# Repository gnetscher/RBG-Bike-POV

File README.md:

RBG-Bike-POV
============

Created for the TI Intern Design Contest 2012

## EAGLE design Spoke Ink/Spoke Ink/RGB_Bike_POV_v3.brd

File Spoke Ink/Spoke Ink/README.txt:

This project was completed in a 5 week time frame.  Please, forgive the somewhat
convoluted nature of our software. finalmainwithstatemachine.c and finalnostatemachine.c both 
contain working versions of our code, but do slightly different things.  With state machine, 
cycles through 3 differnt colored images, and no state machine project one multicolered image.
Thank you for checking out Spoke Ink!

All the best,
George, Val, and Ryan

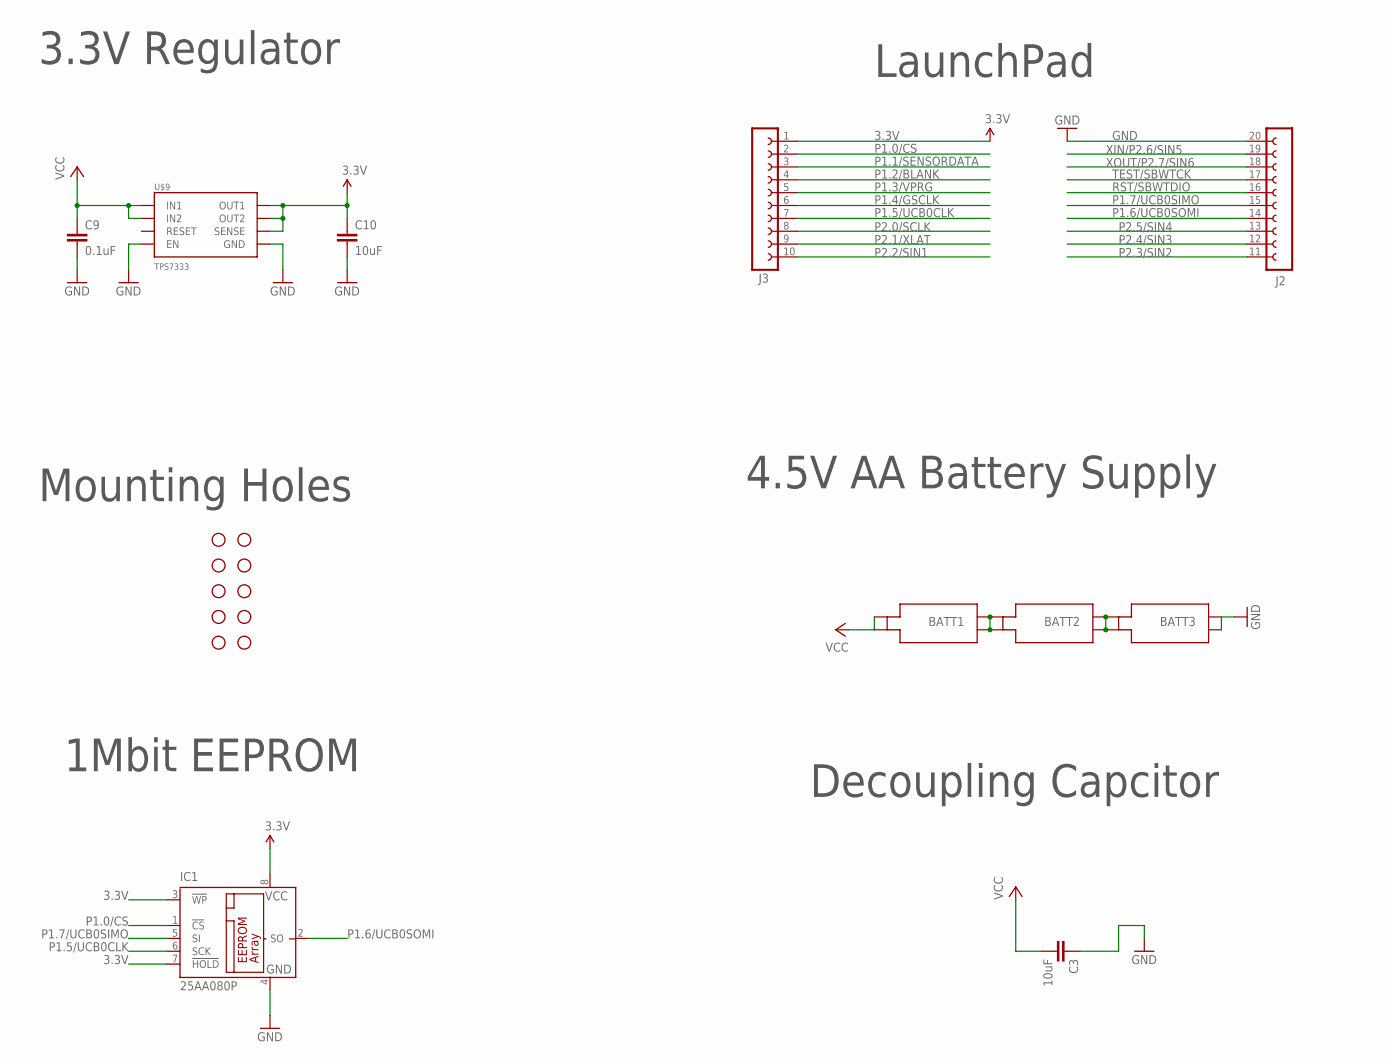
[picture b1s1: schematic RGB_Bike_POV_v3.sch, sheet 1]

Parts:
BATT1, BATT2, BATT3: 1XAA
C3, C10: 10uF; CAP-PTH-SMALL
C9: 0.1uF; CAP-PTH-SMALL
IC1: 25AA080P; DIL8
J2: FE10H
J3: FE10L; FE10
JP1, JP2, JP3, JP4, JP5, JP7, JP25, JP26, JP27, JP28: STAND-OFF
U$9: TPS7333

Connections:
3.3V: C10.1, IC1.3 (!WP), IC1.7 (!HOLD), IC1.8 (VCC), J3.1, U$9.5 (OUT1), U$9.6 (OUT2), U$9.7 (SENSE); also elsewhere on the board
GND: BATT3.N1, BATT3.N2, C3.1, C9.2, C10.2, IC1.4 (GND), J2.20 (10), U$9.1 (GND), U$9.2 (EN); also elsewhere on the board
unnamed: BATT1.N1, BATT1.N2, BATT2.P1, BATT2.P2
unnamed: BATT2.N1, BATT2.N2, BATT3.P1, BATT3.P2
P1.0/CS: IC1.1 (!CS), J3.2
P1.1/SENSORDATA: J3.3; also elsewhere on the board
P1.2/BLANK: J3.4; also elsewhere on the board
P1.3/VPRG: J3.5; also elsewhere on the board
P1.4/GSCLK: J3.6; also elsewhere on the board
P1.5/UCB0CLK: IC1.6 (SCK), J3.7
P1.6/UCB0SOMI: IC1.2 (SO), J2.14 (4)
P1.7/UCB0SIMO: IC1.5 (SI), J2.15 (5)
P2.0/SCLK: J3.8; also elsewhere on the board
P2.1/XLAT: J3.9; also elsewhere on the board
P2.2/SIN1: J3.10; also elsewhere on the board
P2.3/SIN2: J2.11 (1); also elsewhere on the board
P2.4/SIN3: J2.12 (2); also elsewhere on the board
P2.5/SIN4: J2.13 (3); also elsewhere on the board
RST/SBWTDIO: J2.16 (6)
TEST/SBWTCK: J2.17 (7)
VCC: BATT1.P1, BATT1.P2, C3.2, C9.1, U$9.3 (IN1), U$9.4 (IN2); also elsewhere on the board
XIN/P2.6/SIN5: J2.19 (9); also elsewhere on the board
XOUT/P2.7/SIN6: J2.18 (8); also elsewhere on the board

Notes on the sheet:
Mounting Holes
3.3V Regulator
LaunchPad
4.5V AA Battery Supply
1Mbit EEPROM
Decoupling Capcitor

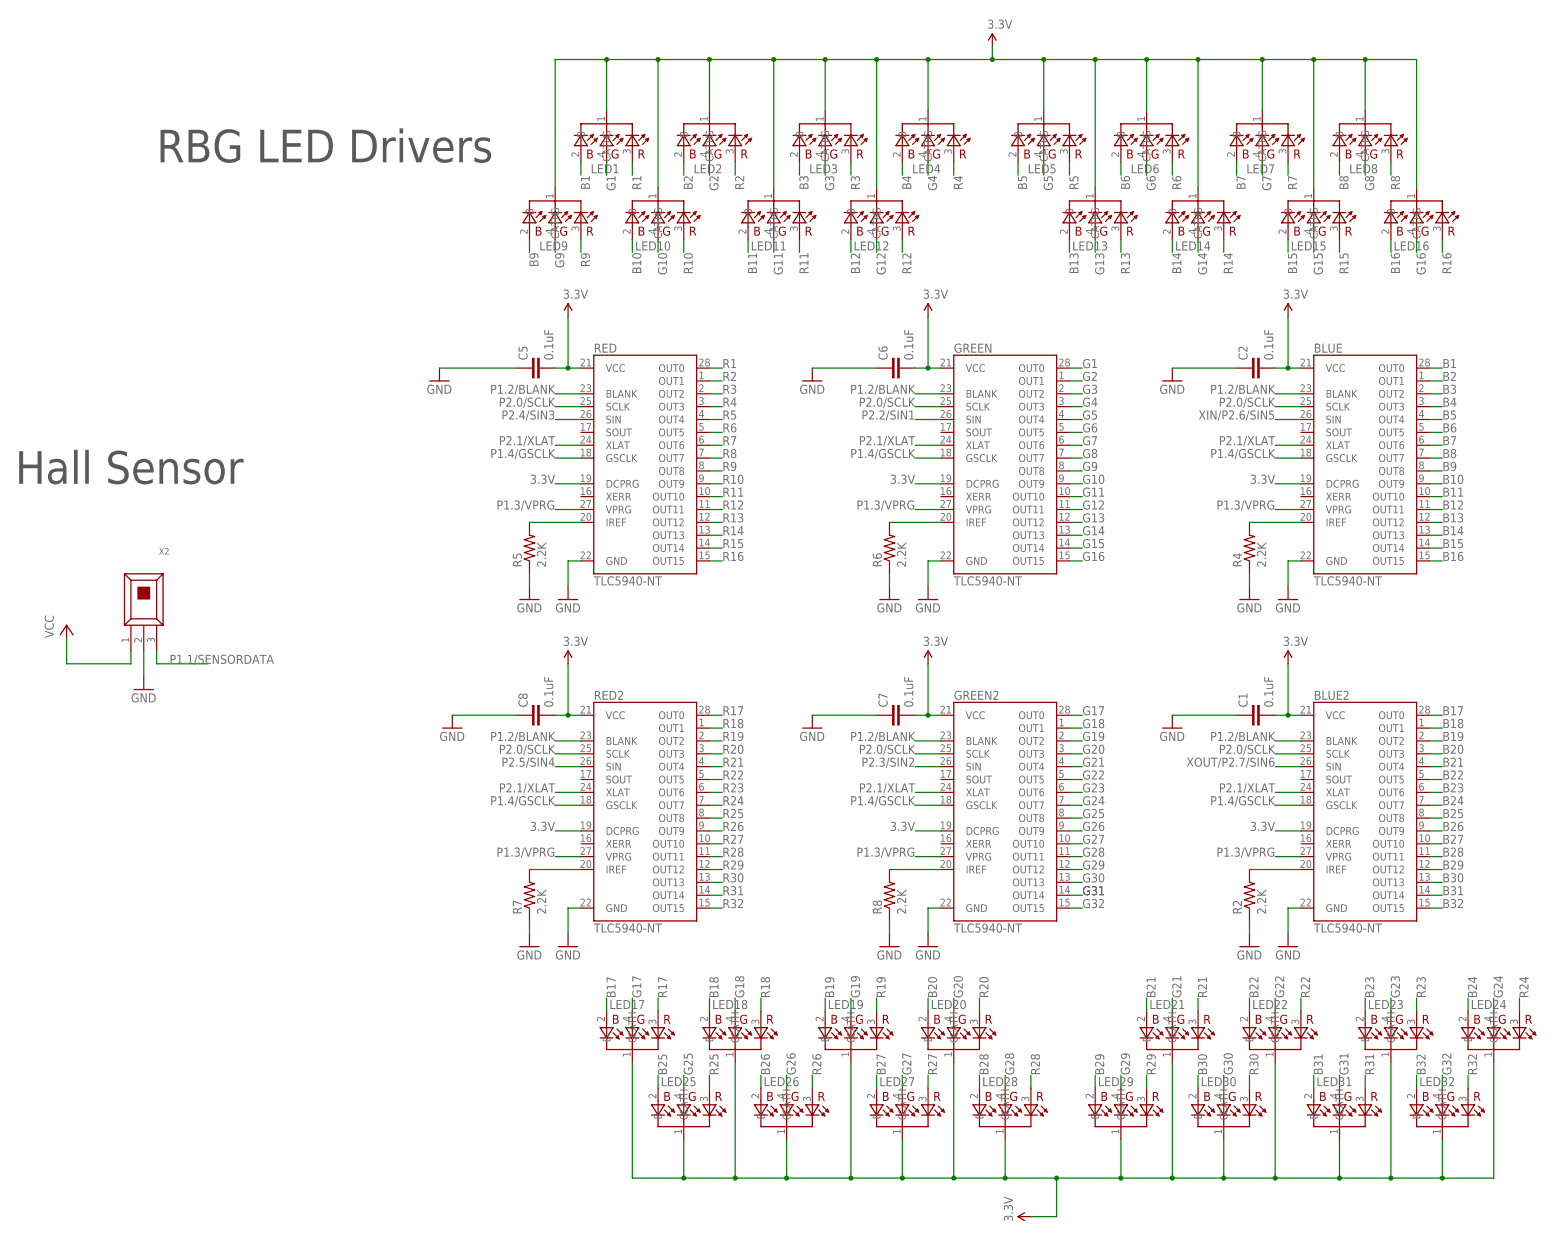
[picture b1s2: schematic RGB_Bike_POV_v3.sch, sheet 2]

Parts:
BLUE, BLUE2: TLC5940-NT; DIL28-3
C1, C2, C5, C6, C7, C8: 0.1uF; CAP-PTH-SMALL
GREEN, GREEN2: TLC5940-NT; DIL28-3
LED1, LED2, LED3, LED4, LED5, LED6, LED7, LED8, LED9, LED10, LED11, LED12, LED13, LED14, LED15, LED16, LED17, LED18, LED19, LED20, LED21, LED22, LED23, LED24, LED25, LED26, LED27, LED28, LED29, LED30, LED31, LED32: LED_SUPERFLUX_RGB_CATH; LED_SUPERFLUX
R2, R4, R5, R6, R7, R8: 2.2K; 1/6W-RES
RED, RED2: TLC5940-NT; DIL28-3
X2: HALLEFFECT; 3SIP

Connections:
3.3V: BLUE.19 (DCPRG), BLUE.21 (VCC), BLUE2.19 (DCPRG), BLUE2.21 (VCC), C1.2, C2.2, C5.2, C6.2, C7.2, C8.2, GREEN.19 (DCPRG), GREEN.21 (VCC), GREEN2.19 (DCPRG), GREEN2.21 (VCC), LED1.1 (CATH), LED2.1 (CATH), LED3.1 (CATH), LED4.1 (CATH), LED5.1 (CATH), LED6.1 (CATH), LED7.1 (CATH), LED8.1 (CATH), LED9.1 (CATH), LED10.1 (CATH), LED11.1 (CATH), LED12.1 (CATH), LED13.1 (CATH), LED14.1 (CATH), LED15.1 (CATH), LED16.1 (CATH), LED17.1 (CATH), LED18.1 (CATH), LED19.1 (CATH), LED20.1 (CATH), LED21.1 (CATH), LED22.1 (CATH), LED23.1 (CATH), LED24.1 (CATH), LED25.1 (CATH), LED26.1 (CATH), LED27.1 (CATH), LED28.1 (CATH), LED29.1 (CATH), LED30.1 (CATH), LED31.1 (CATH), LED32.1 (CATH), RED.19 (DCPRG), RED.21 (VCC), RED2.19 (DCPRG), RED2.21 (VCC); also elsewhere on the board
B1: BLUE.28 (OUT0), LED1.2 (B)
B2: BLUE.1 (OUT1), LED2.2 (B)
B3: BLUE.2 (OUT2), LED3.2 (B)
B4: BLUE.3 (OUT3), LED4.2 (B)
B5: BLUE.4 (OUT4), LED5.2 (B)
B6: BLUE.5 (OUT5), LED6.2 (B)
B7: BLUE.6 (OUT6), LED7.2 (B)
B8: BLUE.7 (OUT7), LED8.2 (B)
B9: BLUE.8 (OUT8), LED9.2 (B)
B10: BLUE.9 (OUT9), LED10.2 (B)
B11: BLUE.10 (OUT10), LED11.2 (B)
B12: BLUE.11 (OUT11), LED12.2 (B)
B13: BLUE.12 (OUT12), LED13.2 (B)
B14: BLUE.13 (OUT13), LED14.2 (B)
B15: BLUE.14 (OUT14), LED15.2 (B)
B16: BLUE.15 (OUT15), LED16.2 (B)
B17: BLUE2.28 (OUT0), LED17.2 (B)
B18: BLUE2.1 (OUT1), LED18.2 (B)
B19: BLUE2.2 (OUT2), LED19.2 (B)
B20: BLUE2.3 (OUT3), LED20.2 (B)
B21: BLUE2.4 (OUT4), LED21.2 (B)
B22: BLUE2.5 (OUT5), LED22.2 (B)
B23: BLUE2.6 (OUT6), LED23.2 (B)
B24: BLUE2.7 (OUT7), LED24.2 (B)
B25: BLUE2.8 (OUT8), LED25.2 (B)
B26: BLUE2.9 (OUT9), LED26.2 (B)
B27: BLUE2.10 (OUT10), LED27.2 (B)
B28: BLUE2.11 (OUT11), LED28.2 (B)
B29: BLUE2.12 (OUT12), LED29.2 (B)
B30: BLUE2.13 (OUT13), LED30.2 (B)
B31: BLUE2.14 (OUT14), LED31.2 (B)
B32: BLUE2.15 (OUT15), LED32.2 (B)
G1: GREEN.28 (OUT0), LED1.4 (G)
G2: GREEN.1 (OUT1), LED2.4 (G)
G3: GREEN.2 (OUT2), LED3.4 (G)
G4: GREEN.3 (OUT3), LED4.4 (G)
G5: GREEN.4 (OUT4), LED5.4 (G)
G6: GREEN.5 (OUT5), LED6.4 (G)
G7: GREEN.6 (OUT6), LED7.4 (G)
G8: GREEN.7 (OUT7), LED8.4 (G)
G9: GREEN.8 (OUT8), LED9.4 (G)
G10: GREEN.9 (OUT9), LED10.4 (G)
G11: GREEN.10 (OUT10), LED11.4 (G)
G12: GREEN.11 (OUT11), LED12.4 (G)
G13: GREEN.12 (OUT12), LED13.4 (G)
G14: GREEN.13 (OUT13), LED14.4 (G)
G15: GREEN.14 (OUT14), LED15.4 (G)
G16: GREEN.15 (OUT15), LED16.4 (G)
G17: GREEN2.28 (OUT0), LED17.4 (G)
G18: GREEN2.1 (OUT1), LED18.4 (G)
G19: GREEN2.2 (OUT2), LED19.4 (G)
G20: GREEN2.3 (OUT3), LED20.4 (G)
G21: GREEN2.4 (OUT4), LED21.4 (G)
G22: GREEN2.5 (OUT5), LED22.4 (G)
G23: GREEN2.6 (OUT6), LED23.4 (G)
G24: GREEN2.7 (OUT7), LED24.4 (G)
G25: GREEN2.8 (OUT8), LED25.4 (G)
G26: GREEN2.9 (OUT9), LED26.4 (G)
G27: GREEN2.10 (OUT10), LED27.4 (G)
G28: GREEN2.11 (OUT11), LED28.4 (G)
G29: GREEN2.12 (OUT12), LED29.4 (G)
G30: GREEN2.13 (OUT13), LED30.4 (G)
G31: GREEN2.14 (OUT14), LED31.4 (G)
G32: GREEN2.15 (OUT15), LED32.4 (G)
GND: BLUE.22 (GND), BLUE2.22 (GND), C1.1, C2.1, C5.1, C6.1, C7.1, C8.1, GREEN.22 (GND), GREEN2.22 (GND), R2.1, R4.1, R5.1, R6.1, R7.1, R8.1, RED.22 (GND), RED2.22 (GND), X2.2; also elsewhere on the board
unnamed: BLUE2.20 (IREF), R2.2
unnamed: BLUE.20 (IREF), R4.2
unnamed: R5.2, RED.20 (IREF)
unnamed: GREEN.20 (IREF), R6.2
unnamed: R7.2, RED2.20 (IREF)
unnamed: GREEN2.20 (IREF), R8.2
P1.1/SENSORDATA: X2.3; also elsewhere on the board
P1.2/BLANK: BLUE.23 (BLANK), BLUE2.23 (BLANK), GREEN.23 (BLANK), GREEN2.23 (BLANK), RED.23 (BLANK), RED2.23 (BLANK); also elsewhere on the board
P1.3/VPRG: BLUE.27 (VPRG), BLUE2.27 (VPRG), GREEN.27 (VPRG), GREEN2.27 (VPRG), RED.27 (VPRG), RED2.27 (VPRG); also elsewhere on the board
P1.4/GSCLK: BLUE.18 (GSCLK), BLUE2.18 (GSCLK), GREEN.18 (GSCLK), GREEN2.18 (GSCLK), RED.18 (GSCLK), RED2.18 (GSCLK); also elsewhere on the board
P2.0/SCLK: BLUE.25 (SCLK), BLUE2.25 (SCLK), GREEN.25 (SCLK), GREEN2.25 (SCLK), RED.25 (SCLK), RED2.25 (SCLK); also elsewhere on the board
P2.1/XLAT: BLUE.24 (XLAT), BLUE2.24 (XLAT), GREEN.24 (XLAT), GREEN2.24 (XLAT), RED.24 (XLAT), RED2.24 (XLAT); also elsewhere on the board
P2.2/SIN1: GREEN.26 (SIN); also elsewhere on the board
P2.3/SIN2: GREEN2.26 (SIN); also elsewhere on the board
P2.4/SIN3: RED.26 (SIN); also elsewhere on the board
P2.5/SIN4: RED2.26 (SIN); also elsewhere on the board
R1: LED1.3 (R), RED.28 (OUT0)
R2: LED2.3 (R), RED.1 (OUT1)
R3: LED3.3 (R), RED.2 (OUT2)
R4: LED4.3 (R), RED.3 (OUT3)
R5: LED5.3 (R), RED.4 (OUT4)
R6: LED6.3 (R), RED.5 (OUT5)
R7: LED7.3 (R), RED.6 (OUT6)
R8: LED8.3 (R), RED.7 (OUT7)
R9: LED9.3 (R), RED.8 (OUT8)
R10: LED10.3 (R), RED.9 (OUT9)
R11: LED11.3 (R), RED.10 (OUT10)
R12: LED12.3 (R), RED.11 (OUT11)
R13: LED13.3 (R), RED.12 (OUT12)
R14: LED14.3 (R), RED.13 (OUT13)
R15: LED15.3 (R), RED.14 (OUT14)
R16: LED16.3 (R), RED.15 (OUT15)
R17: LED17.3 (R), RED2.28 (OUT0)
R18: LED18.3 (R), RED2.1 (OUT1)
R19: LED19.3 (R), RED2.2 (OUT2)
R20: LED20.3 (R), RED2.3 (OUT3)
R21: LED21.3 (R), RED2.4 (OUT4)
R22: LED22.3 (R), RED2.5 (OUT5)
R23: LED23.3 (R), RED2.6 (OUT6)
R24: LED24.3 (R), RED2.7 (OUT7)
R25: LED25.3 (R), RED2.8 (OUT8)
R26: LED26.3 (R), RED2.9 (OUT9)
R27: LED27.3 (R), RED2.10 (OUT10)
R28: LED28.3 (R), RED2.11 (OUT11)
R29: LED29.3 (R), RED2.12 (OUT12)
R30: LED30.3 (R), RED2.13 (OUT13)
R31: LED31.3 (R), RED2.14 (OUT14)
R32: LED32.3 (R), RED2.15 (OUT15)
VCC: X2.1; also elsewhere on the board
XIN/P2.6/SIN5: BLUE.26 (SIN); also elsewhere on the board
XOUT/P2.7/SIN6: BLUE2.26 (SIN); also elsewhere on the board

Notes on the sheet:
RBG LED Drivers
Hall Sensor

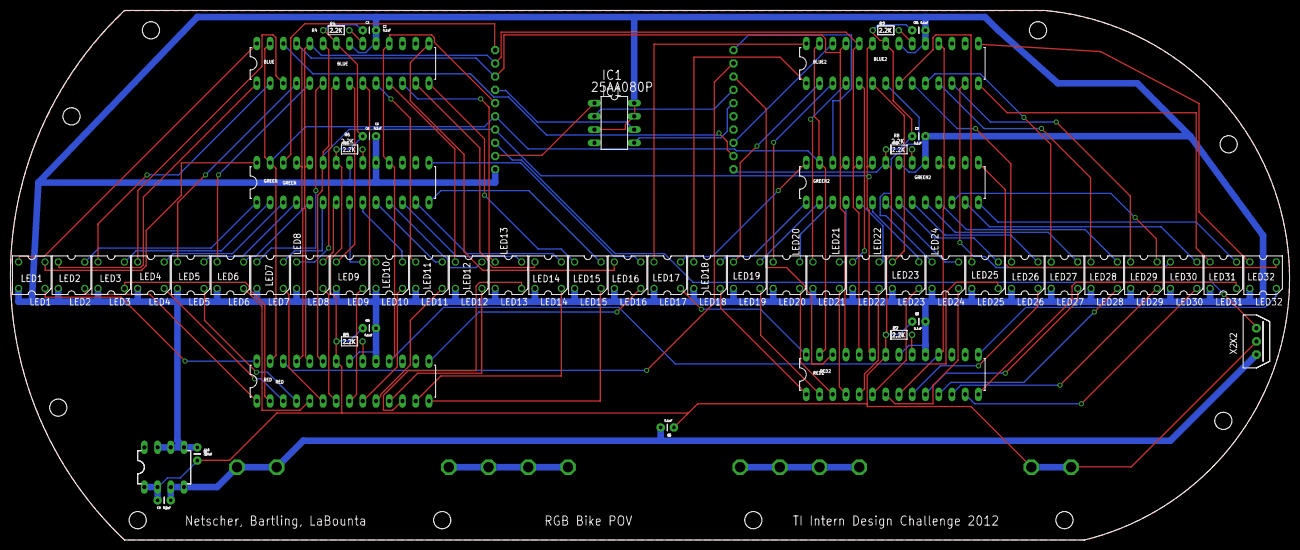
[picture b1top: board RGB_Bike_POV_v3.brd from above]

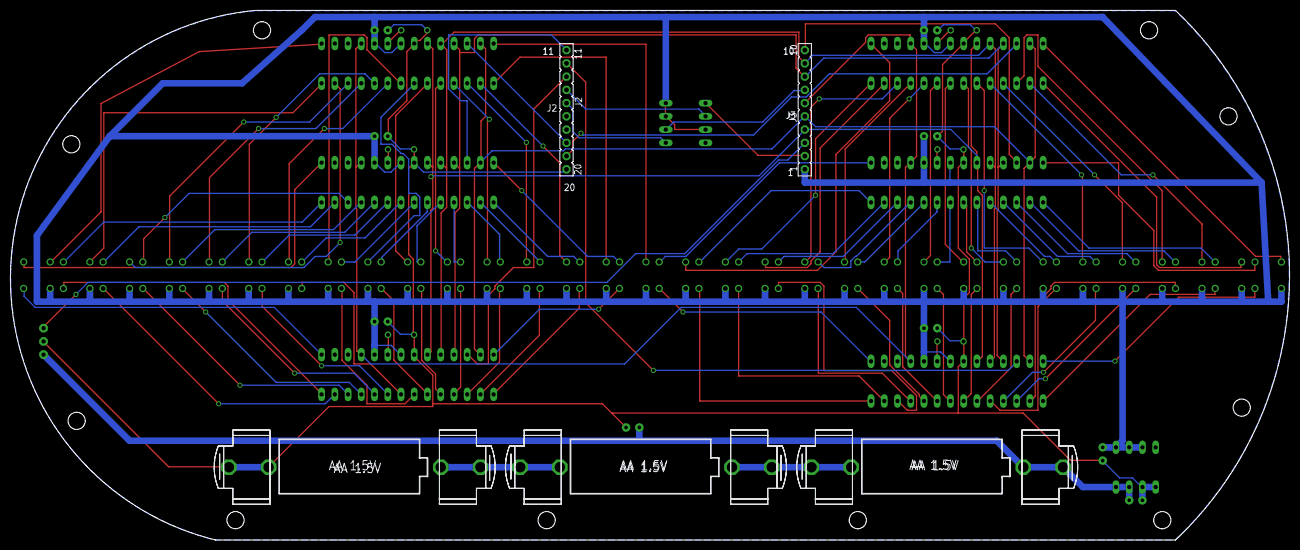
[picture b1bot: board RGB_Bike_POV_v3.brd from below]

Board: 2 copper layers, 245.4 x 101.6 mm, 71 parts (5 on the bottom side), 123 nets.

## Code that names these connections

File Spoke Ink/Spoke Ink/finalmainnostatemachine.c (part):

//Great thanks to TI_RGB_TABLE for their code influence
//PIN1.0=CS
//PIN1.1=SENSORDATA
//PIN1.2=BLANK
//PIN1.3=VPRG
//PIN1.4=SMCLCK (GSCLCK)
//PIN1.5=UCB0CLK
//PIN1.6=UCB0SOMI
//PIN1.7=UCB0SIMO
//PIN2.0=SCLK
//PIN2.1=XLAT
//PIN2.2=SIN1
//PIN2.3=SIN2
//PIN2.4=SIN3
//PIN2.5=SIN4
//PIN2.6=SIN5
//PIN2.7=SIN6

#define XLAT BIT1
#define SIN1 BIT2
#define SIN2 BIT3
#define SIN3 BIT4
#define SIN4 BIT5
#define SIN5 BIT6
#define SIN6 BIT7
#define SCLK BIT0
#define BLANK BIT2
#define VPRG BIT3 //p1
#define GSCLK BIT4 //p2
#define NUM_LEDS (96)
unsigned int number_cycles;
volatile unsigned char need_xlat = 0;
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    // set all control lines to 0
    P2OUT &= ~XLAT;
    P2OUT &= ~SIN1;
    P2OUT &= ~SIN2;				//Remember to set correct pins some p1
    P2OUT &= ~SIN3;
    P2OUT &= ~SIN4;
    P2OUT &= ~SIN5;
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
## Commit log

2012-08-11 adding final spoke ink project files
